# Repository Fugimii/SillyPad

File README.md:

# Silly Pad!

A 4x4 macropad I made with [KiCad](https://www.kicad.org/) and [Fusion 360](https://www.autodesk.com/products/fusion-360/personal) to learn how to make pcbs!

You can find footprints and 3D Models in `SillyPad.pretty`

Components used:
 - 1 x [Pi Pico Clone Board](https://www.aliexpress.com/item/1005008777234500.html?spm=a2g0o.order_list.order_list_main.11.f56418023OoaDa)
 - 16 x [3 Pin Cherry MX Switches](https://www.aliexpress.com/item/1005002378701948.html?spm=a2g0o.order_list.order_list_main.29.f56418023OoaDa)
 - 2 x [EC11 rotary encoders](https://www.aliexpress.com/item/10000000931574.html?spm=a2g0o.order_list.order_list_main.23.f56418023OoaDa)
 - 1 x [0.96 inch SSD1315 128x64 OLED I2C Screen](https://www.aliexpress.com/item/1005006985022252.html?spm=a2g0o.order_list.order_list_main.17.f56418023OoaDa)(SSD1305s will also work)
 - 16 x [1N4148 Diodes](https://www.aliexpress.com/item/1005006713281350.html?spm=a2g0o.order_list.order_list_main.5.f56418023OoaDa)

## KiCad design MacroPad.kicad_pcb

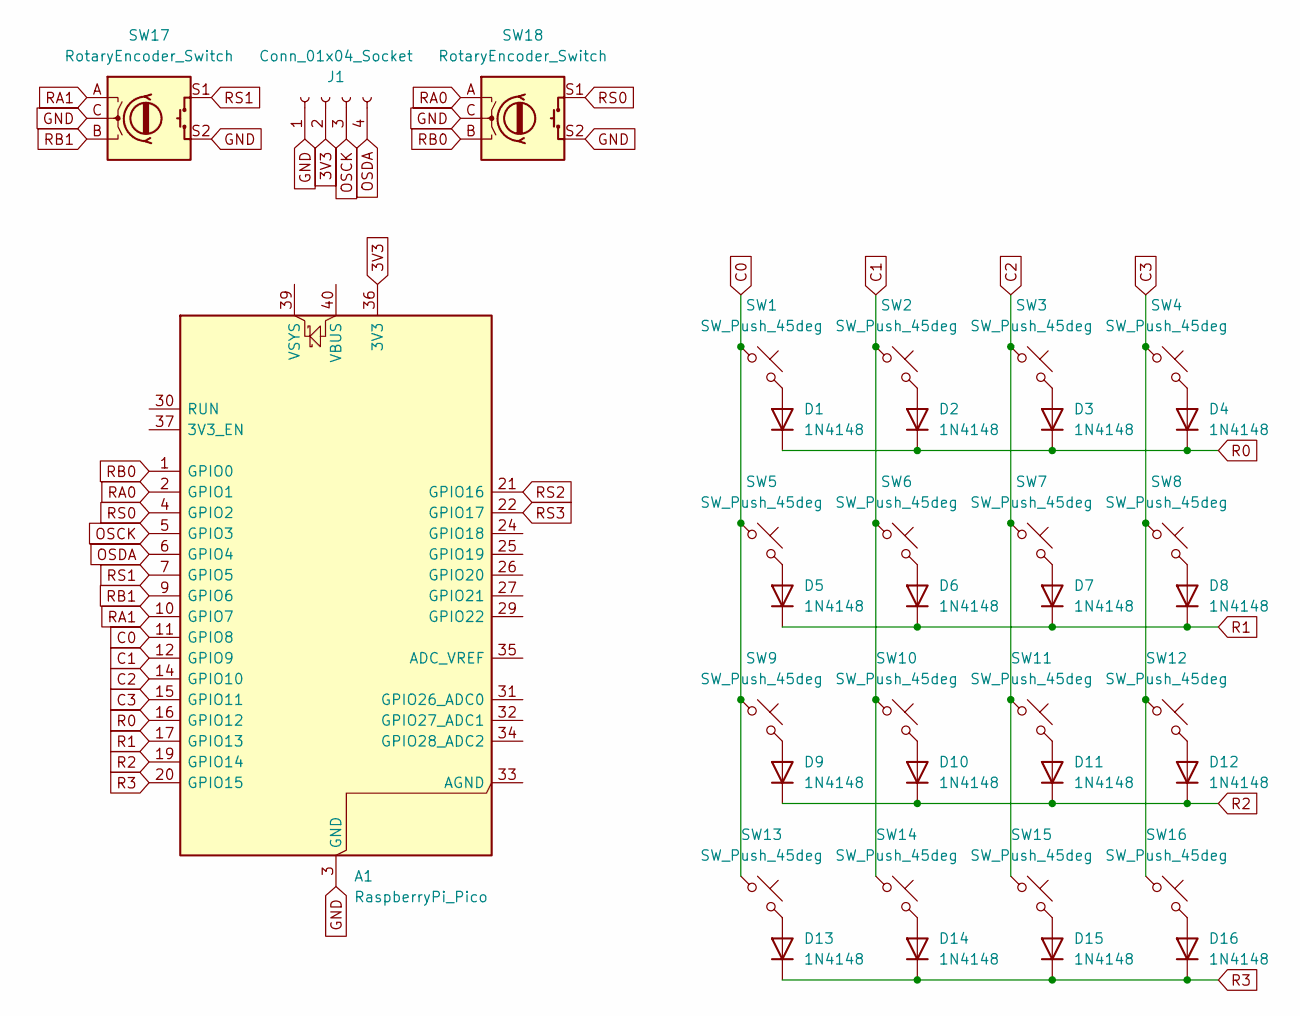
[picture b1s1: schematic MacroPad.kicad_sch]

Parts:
A1: RaspberryPi_Pico; RaspberryPi_Pico_Common_THT
D1, D2, D3, D4, D5, D6, D7, D8, D9, D10, D11, D12, D13, D14, D15, D16: 1N4148; D_DO-35_SOD27_P7.62mm_Horizontal
J1: Conn_01x04_Socket; MODULE_DM-OLED096-636
SW1, SW2, SW3, SW4, SW5, SW6, SW7, SW8, SW9, SW10, SW11, SW12, SW13, SW14, SW15, SW16: SW_Push_45deg; SW_Cherry_MX_Plate_1.00u
SW17, SW18: RotaryEncoder_Switch; RotaryEncoder_Alps_EC11E-Switch_Vertical_H20mm

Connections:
3V3: A1.36 (3V3), J1.2
C0: A1.11 (GPIO8), SW1.1, SW5.1, SW9.1, SW13.1
C1: A1.12 (GPIO9), SW2.1, SW6.1, SW10.1, SW14.1
C2: A1.14 (GPIO10), SW3.1, SW7.1, SW11.1, SW15.1
C3: A1.15 (GPIO11), SW4.1, SW8.1, SW12.1, SW16.1
GND: A1.3 (GND), A1.8 (GND), A1.13 (GND), A1.18 (GND), A1.23 (GND), A1.28 (GND), A1.38 (GND), J1.1, SW17.C, SW17.S2, SW18.C, SW18.S2
unnamed: D1.2 (A), SW1.2
unnamed: D2.2 (A), SW2.2
unnamed: D3.2 (A), SW3.2
unnamed: D4.2 (A), SW4.2
unnamed: D5.2 (A), SW5.2
unnamed: D6.2 (A), SW6.2
unnamed: D7.2 (A), SW7.2
unnamed: D8.2 (A), SW8.2
unnamed: D9.2 (A), SW9.2
unnamed: D10.2 (A), SW10.2
unnamed: D11.2 (A), SW11.2
unnamed: D12.2 (A), SW12.2
unnamed: D13.2 (A), SW13.2
unnamed: D14.2 (A), SW14.2
unnamed: D15.2 (A), SW15.2
unnamed: D16.2 (A), SW16.2
OSCK: A1.5 (GPIO3), J1.3
OSDA: A1.6 (GPIO4), J1.4
R0: A1.16 (GPIO12), D1.1 (K), D2.1 (K), D3.1 (K), D4.1 (K)
R1: A1.17 (GPIO13), D5.1 (K), D6.1 (K), D7.1 (K), D8.1 (K)
R2: A1.19 (GPIO14), D9.1 (K), D10.1 (K), D11.1 (K), D12.1 (K)
R3: A1.20 (GPIO15), D13.1 (K), D14.1 (K), D15.1 (K), D16.1 (K)
RA0: A1.2 (GPIO1), SW18.A
RA1: A1.10 (GPIO7), SW17.A
RB0: A1.1 (GPIO0), SW18.B
RB1: A1.9 (GPIO6), SW17.B
RS0: A1.4 (GPIO2), SW18.S1
RS1: A1.7 (GPIO5), SW17.S1
RS2: A1.21 (GPIO16)
RS3: A1.22 (GPIO17)

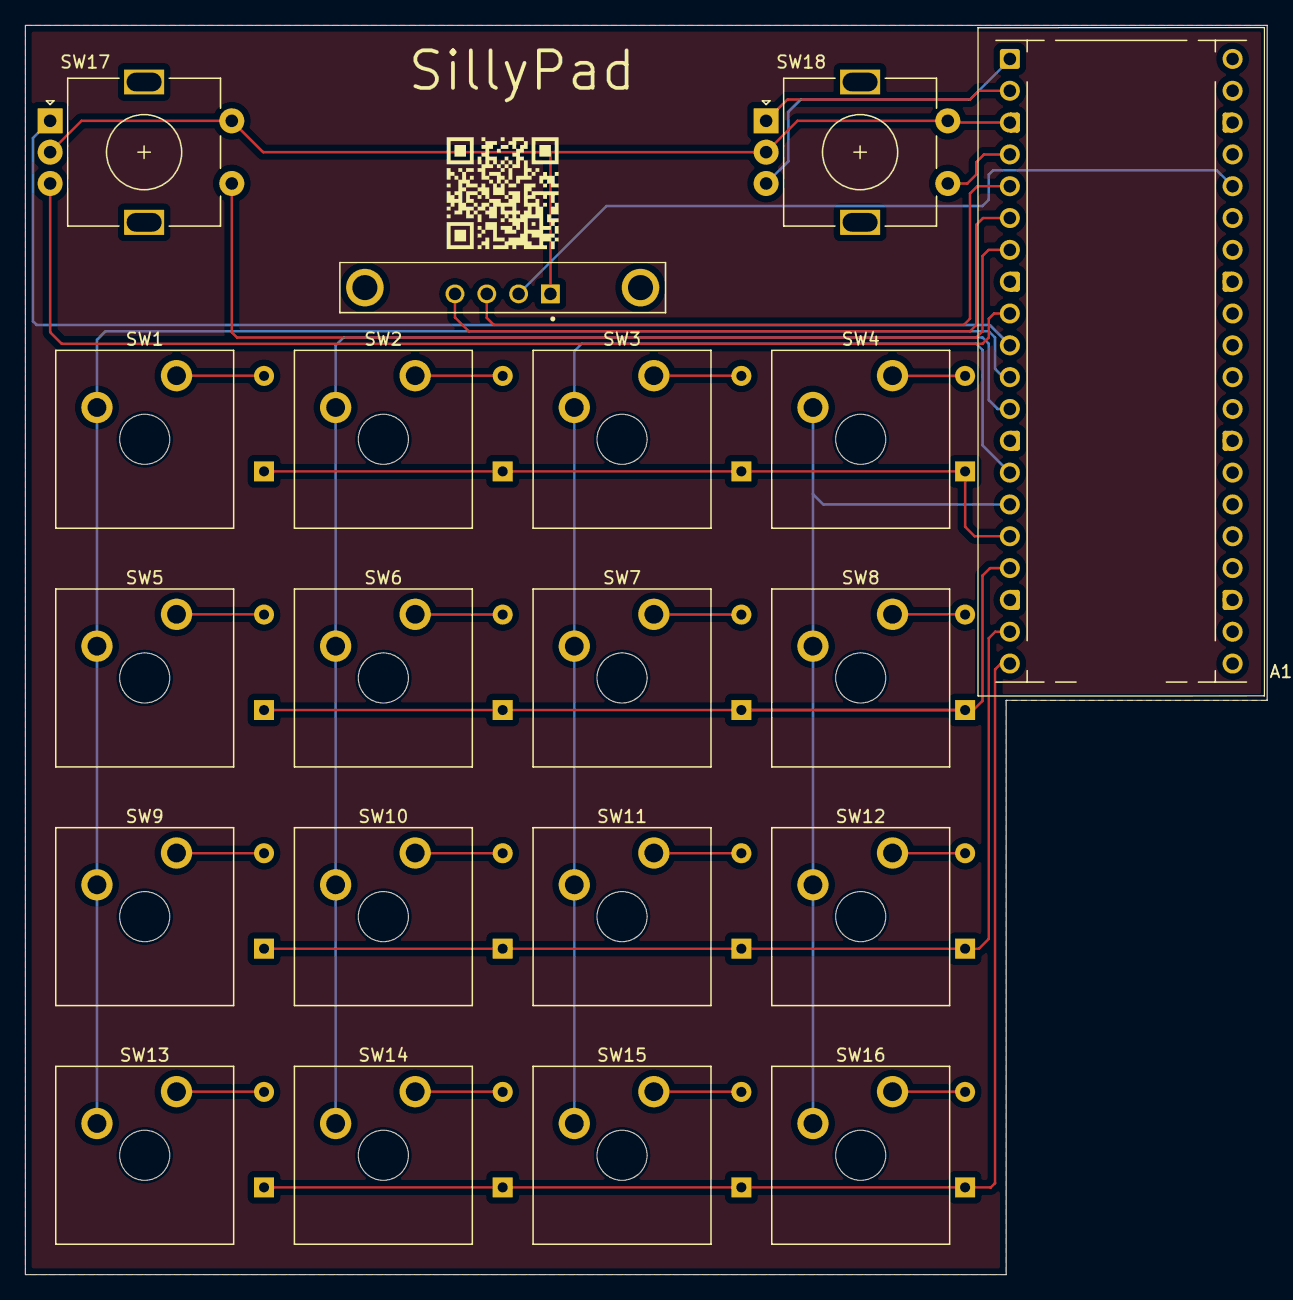
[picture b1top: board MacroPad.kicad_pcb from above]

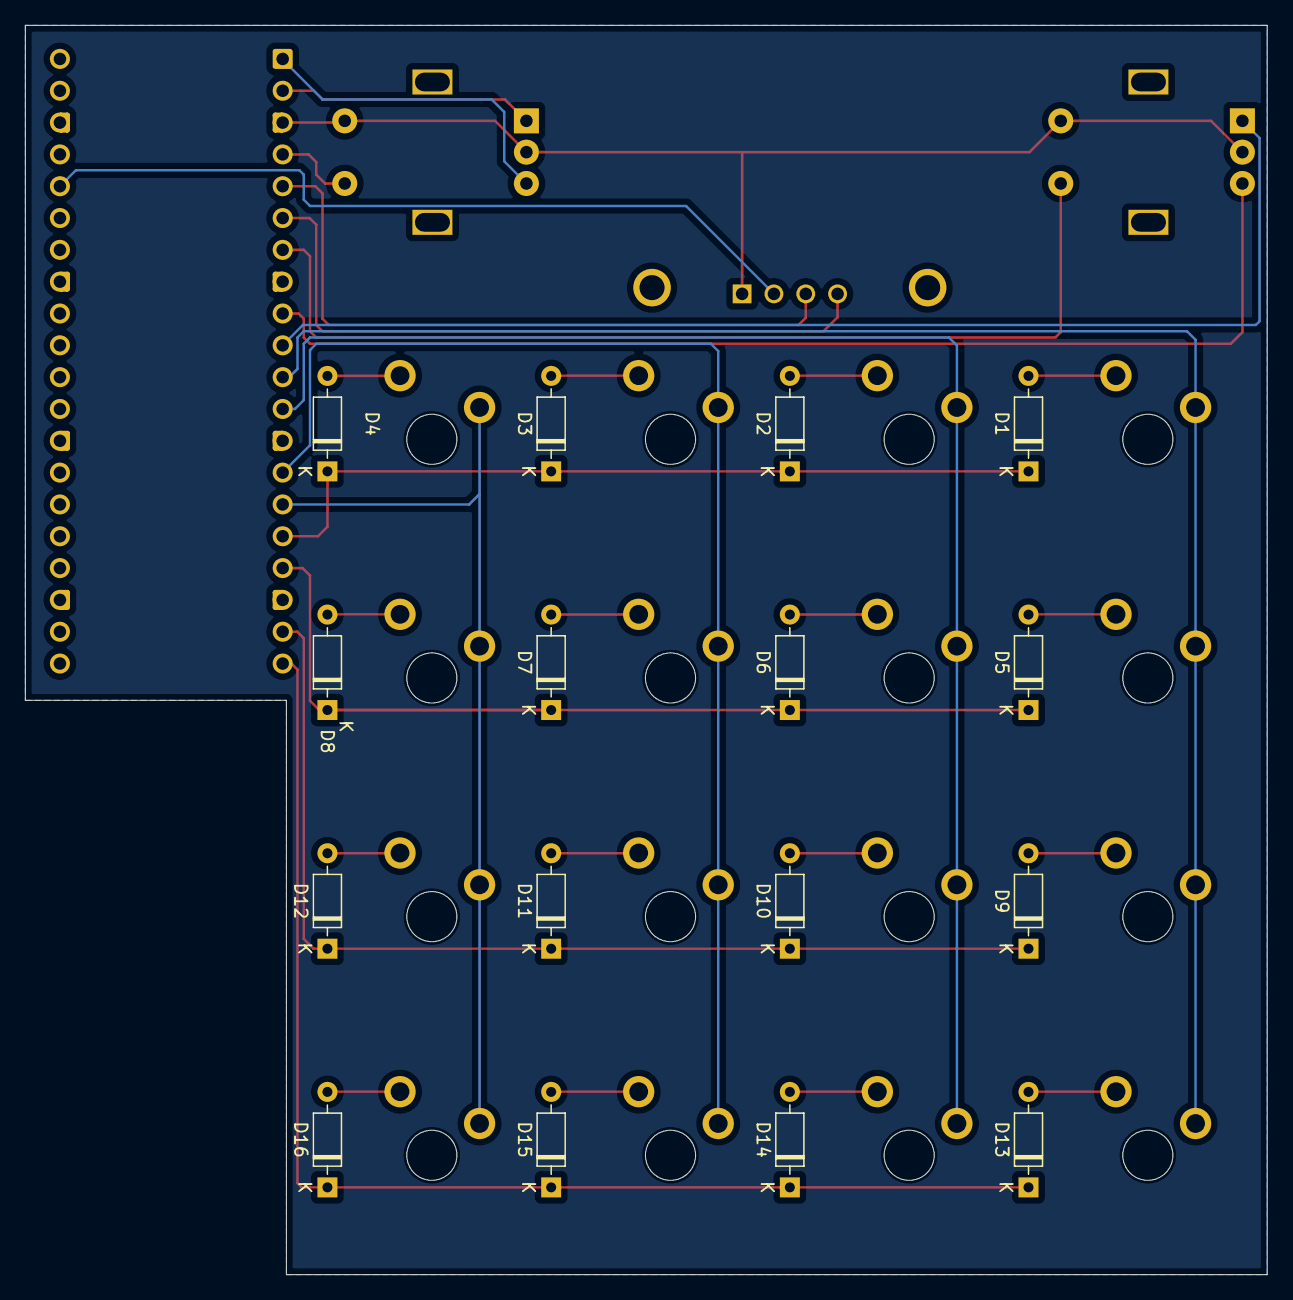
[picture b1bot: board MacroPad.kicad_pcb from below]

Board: 2 copper layers, 99.1 x 99.7 mm, 36 parts (16 on the bottom side), 34 nets.

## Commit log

2025-05-13 Init
2025-05-13 Added QR code and name
2025-05-13 Added models & footprints to the repo
2025-05-13 Forgot about the diodes!
2025-05-13 Footprints
2025-06-11 Added qmk code
2025-06-17 Added the basics of the website
2025-06-17 Renamed the qmk folder
2025-06-17 Renamed the website folder to docs/ for github pages
2025-06-20 Rewrote entire website :skull:
2025-06-20 Made everything very fancy
2025-06-20 Made the make it yourself button do something
2025-06-22 Added icons to feature cards and removed the hero image shadow
2025-06-22 Made the title fancy
2025-12-16 Added image of sillypad
2025-12-16 Make image not look like butt
2025-12-16 Revise readme with image and project details
    Updated the readme with a new image link and enhanced project description.
2025-12-16 Update README with image
